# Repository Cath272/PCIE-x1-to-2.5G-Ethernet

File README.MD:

# PCIE x1 to 2.5Gb Ethernet
 Pcie to 2.5GbE  using RTL8125

 ## RTL8125BG 

  - Integrated 10/100/1000M/2.5G transceiver

  - 

 ## TPS

 - 5V to 0.95V DC-DC (1A)

 ## LX82405SP
 -2.5GbE Magnetics 
## PCB 
This board uses a 4 layer stackup with a  1.6mm thickness:

- POWER/SIGNAL

- GND
  
- GND
  
- POWER/SIGNAL

High Speed diferential lines need a refrence ground plane so internal planes are ground referance planes for the High speed pcie lanes

TBD: photos and schematic
### Schematic:

## PCB Screenshots

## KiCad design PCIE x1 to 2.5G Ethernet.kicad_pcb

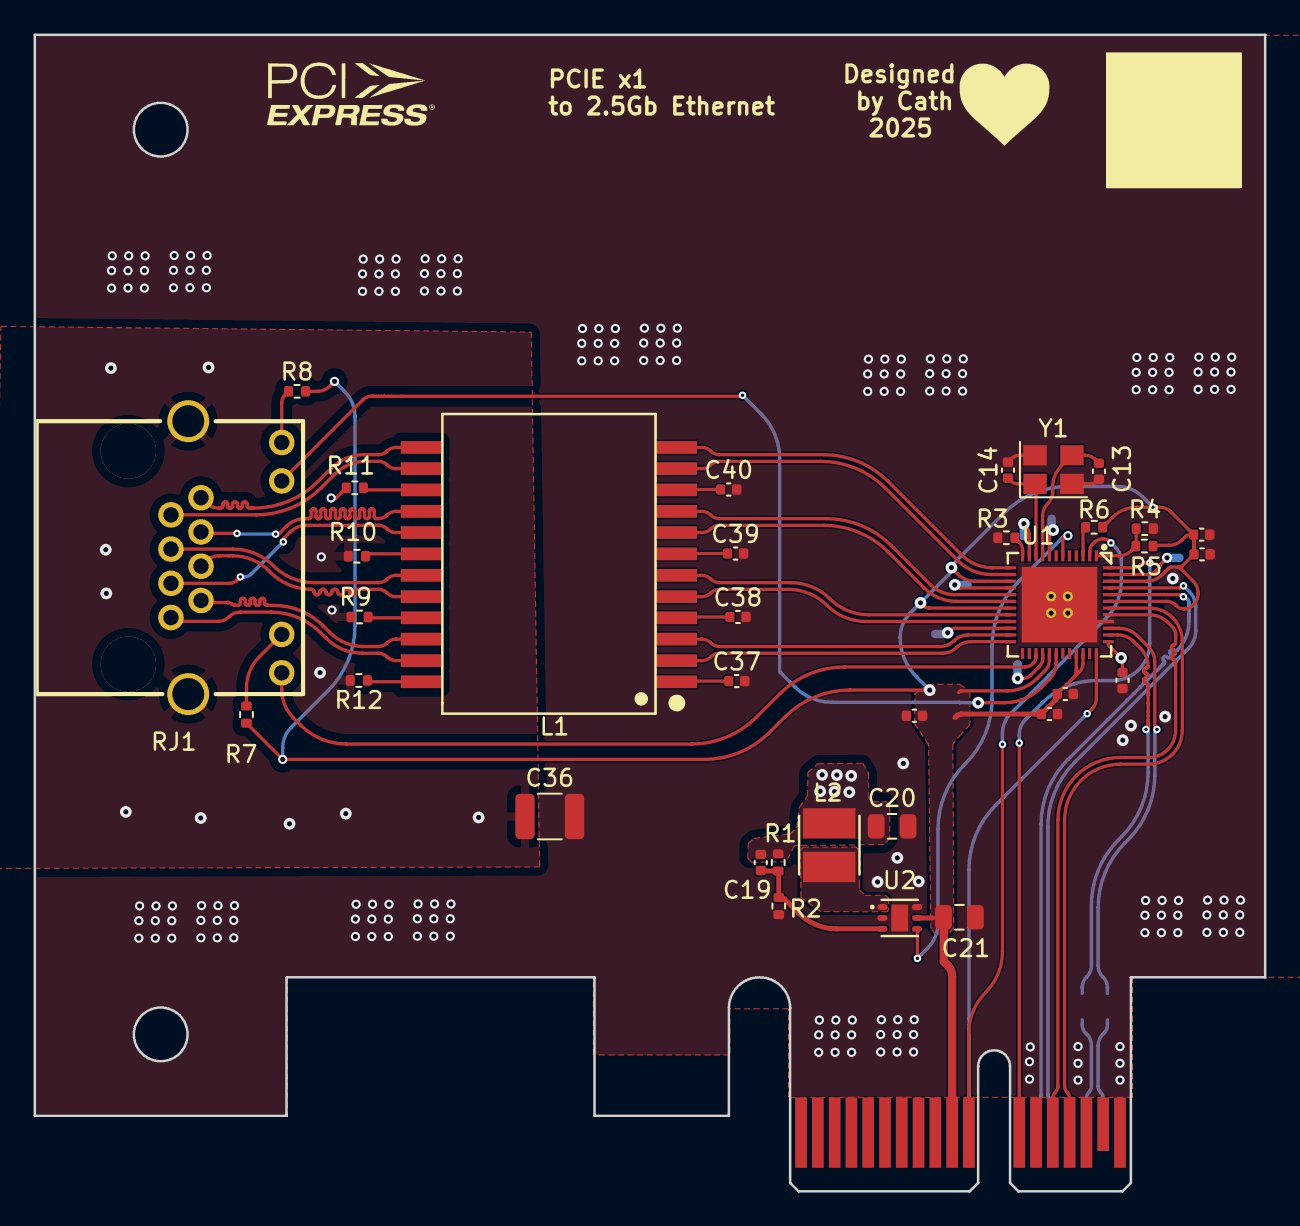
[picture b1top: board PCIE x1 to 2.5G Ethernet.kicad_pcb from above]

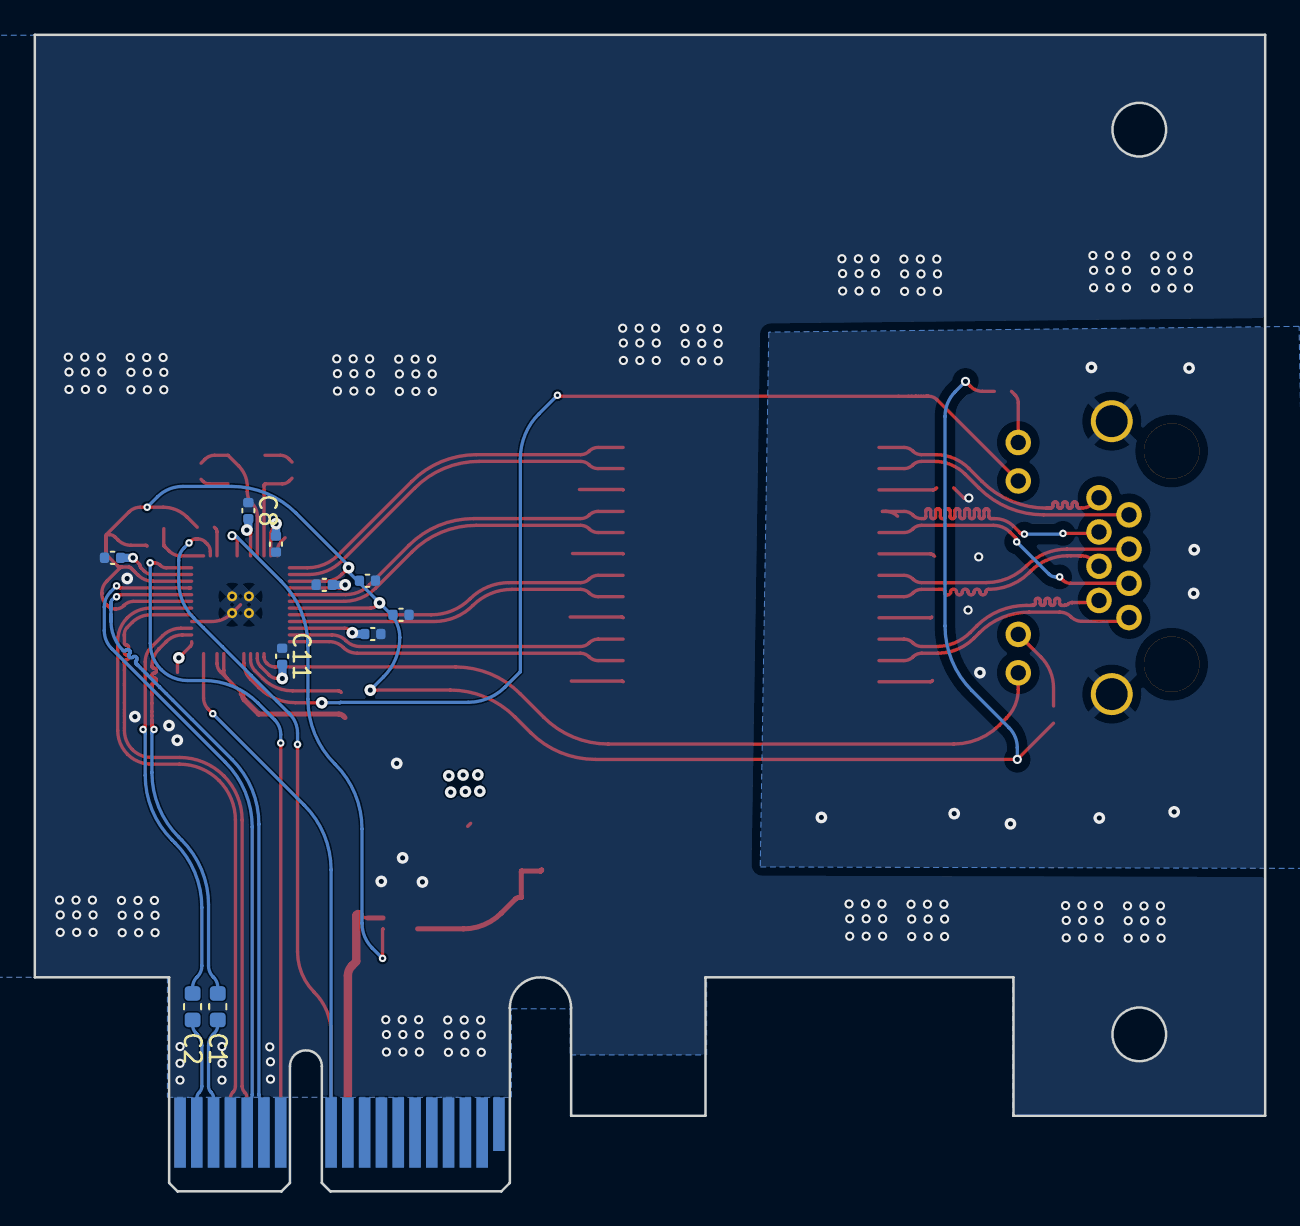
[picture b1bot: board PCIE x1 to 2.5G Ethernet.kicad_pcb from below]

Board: 4 copper layers, 73.3 x 68.9 mm, 46 parts (10 on the bottom side), 51 nets.

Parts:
C1, C2: 100n; C_0603_1608Metric
C3, C4, C5, C6, C7, C8, C9, C10, C11, C12, C15, C16, C17, C18, C37, C38, C39, C40: 100nF; C_0402_1005Metric
C13, C14: 18pF; C_0402_1005Metric
C19: 22pF; C_0402_1005Metric
C20, C21: 10uF; C_0805_2012Metric
C36: 1nF 2kV; C_1210_3225Metric
J1: PCIexpress_bracket; PCIexpress_bracket_low
J2: PCIexpress_x1
L1: HY602401; XFMR-SMD_HY602401
L2: 2.2uH; IND-SMD_L3.5-W3.0
R1: 160k; R_0402_1005Metric
R2: 280k; R_0402_1005Metric
R3: 2.49k; R_0402_1005Metric
R4, R6: 15K; R_0402_1005Metric
R5: 1K; R_0402_1005Metric
R7, R8: 220R; R_0402_1005Metric
R9, R10, R11, R12: 75R; R_0402_1005Metric
RJ1: R-RJ45R08P-C000; RJ45-TH_R-RJ45R08P-C000
U1: RTL8125BG-CG; TQFN-48_L6.0-W6.0-P0.40-BL-EP4.5
U2: TPS62590DRVT; WSON-6_L2.0-W2.0-P0.65-TL-EP
Y1: 25Mhz; Crystal_SMD_3225-4Pin_3.2x2.5mm

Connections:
+0.95V: C3.2, C6.2, C7.2, C8.2, C10.2, C11.2, C15.2, C19.1, C20.1, L2.1, R1.1, U1.8 (DVDD09), U1.11 (AVDD09), U1.16 (AVDD09), U1.22 (AVDD09), U1.28 (DVDD09), U1.37 (EVDD09), U1.47 (DVDD09)
+3.3VA: C4.2, C5.2, C9.2, C12.2, C16.2, C17.2, C18.2, C21.1, J2.B10 (+3.3V_aux), R5.1, R6.1, R7.1, R8.2, U1.15 (AVDD33), U1.19 (AVDD33), U1.29 (DVDD33), U1.33 (AVDD33), U1.34 (AVDD33_XTAL), U1.43 (EVDD33), U1.46 (DVDD33), U2.5 (VIN)
/Connectors/PCIexpress_connector/_PER0_N: C2.1, J2.A17 (PERn0)
/Connectors/PCIexpress_connector/_PER0_P: C1.2, J2.A16 (PERp0)
CLK_REQ: J2.B12 (CLK_REQ), U1.48 (CLKREQB)
ETH_GND: C36.1, R9.2, R10.2, R11.2, R12.2, RJ1.13 (S), RJ1.14 (S)
GND: C3.1, C4.1, C5.1, C6.1, C7.1, C8.1, C9.1, C10.1, C11.1, C12.1, C13.1, C14.2, C15.1, C16.1, C17.1, C18.1, C20.2, C21.2, C36.2, C37.2, C38.2, C39.2, C40.2, J2.A4 (GND), J2.A12 (GND), J2.A15 (GND), J2.A18 (GND), J2.B4 (GND), J2.B7 (GND), J2.B13 (GND), J2.B16 (GND), J2.B18 (GND), R2.2, R3.1, R4.1, U1.40 (GND), U1.49 (GND), U2.2 (MODE), U2.6 (GND), U2.7 (EP), Y1.2, Y1.4
LED0: RJ1.10 (L-), U1.30 (LED0/EEDI/SPISI/SDA)
LED1: RJ1.12 (R-), U1.27 (LED1/EESK/SPISC)
MD1+: L1.13 (MX4-), RJ1.8
MD1-: L1.14 (MX4+), RJ1.7
MD2+: L1.16 (MX3-), RJ1.6
MD2-: L1.17 (MX3+), RJ1.3
MD3+: L1.19 (MX2-), RJ1.5
MD3-: L1.20 (MX2+), RJ1.4
MD4+: L1.22 (MX1-), RJ1.2
MD4-: L1.23 (MX1+), RJ1.1
MDIN0: L1.11 (TD4+), U1.14 (MDIN0)
MDIN1: L1.8 (TD3+), U1.18 (MDIN1)
MDIN2: L1.5 (TD2+), U1.21 (MDIN2)
MDIN3: L1.2 (TD1+), U1.24 (MDIN3)
MDIP0: L1.12 (TD4-), U1.13 (MDIP0)
MDIP1: L1.9 (TD3-), U1.17 (MDIP1)
MDIP2: L1.6 (TD2-), U1.20 (MDIP2)
MDIP3: L1.3 (TD1-), U1.23 (MDIP3)
unnamed: L1.24 (MCT1), R12.1
unnamed: L1.21 (MCT2), R9.1
unnamed: L1.18 (MCT3), R10.1
unnamed: L1.15 (MCT4), R11.1
unnamed: C37.1, L1.1 (TCT1)
unnamed: C38.1, L1.4 (TCT2)
unnamed: C39.1, L1.7 (TCT3)
unnamed: C40.1, L1.10 (TCT4)
unnamed: R8.1, RJ1.9 (L+)
unnamed: R7.2, RJ1.11 (R+)
unnamed: C14.1, U1.10 (CKXTAL1), Y1.1
unnamed: C13.2, U1.9 (CKXTAL2), Y1.3
unnamed: R6.2, U1.3 (GPI)
unnamed: R4.2, R5.2, U1.1 (ISOLATEB)
unnamed: R3.2, U1.12 (RSET)
unnamed: C19.2, R1.2, R2.1, U2.3 (FB)
unnamed: L2.2, U2.1 (SW)
PER0+: C1.1, U1.38 (HSOP)
PER0-: C2.2, U1.39 (HSON)
PERST: J2.A11 (~PERST), U1.36 (PERSTB)
PET0+: J2.B14 (PETp0), U1.41 (HSIP)
PET0-: J2.B15 (PETn0), U1.42 (HSIN)
REFCLK+: J2.A13 (REFCLK+), U1.44 (REFCLK_P)
REFCLK-: J2.A14 (REFCLK-), U1.45 (REFCLK_N)
REG_EN: U1.6 (POW_EXT_SWR), U2.4 (EN)
WAKE: J2.B11 (~WAKE), U1.2 (LANWAKEB)
